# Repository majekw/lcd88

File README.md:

lcd88
=====

Open source, flexible PPM coder/mixer/brain for R/C transmitter.

Main website: http://majek.mamy.to/lcd88

About
-----

LCD88 is software for Atmega88/168/328 controller to generate PPM waveform.
It also support simple keyboard and graphic LCD.
Main goal of this project is to make cheap and powerful replacement for old
R/C transmitters. So, for few $ you could retrofit your old TX to make
fully programmable 8 channels (or more) transmitter.

Configuring
-----------

1. Open Makefile
2. Uncomment one of defines with processor type (M88, M168 or M328)
3. Uncomment clock selection (FCK16 for 16MHz or FCK11 for 11.0592MHz).
If you need another clock, you need to hack a little in lcd88.asm,
but don't set it higher than 16MHz!
4. Open lcd-s65.asm
5. Uncomment one define with lcd_l2f50, lcd_ls020 or lcd_st7735 depending
on you lcd hardware

Compiling/burning
---------

You need [AVRA](http://avra.sourceforge.net) to compile it.
Also some 'make' and Linux environment could help :-)
If you have Linux, just type 'make' and it should make everything.
Right now it's not very friendly for other systems, so in case of troubles,
look into Makefile and try make all steps manually.

After succesful compilation you should have 2 .hex files:
- lcd88.hex
- bootloader.hex

Bootloader image you must burn using USBASP or other 'traditional'
programmer. Then you could transfer lcd88.hex converted to raw binary
over serial.

Hardware
--------

Of course, you need some hardware to run this software :-)

Processors supported:
- Atmega88 (but support for it will be discontinued soon)
- Atmega168 and Atmega328 (both you can find on Arduino boards)

Processor clock supported: up to 16MHz (so, everything below or equal
will run fine).

Graphic LCD:
- 176x132 lcd used in old Siemens S65 phones, L2F50 and LS020 versions
- cheap 1.8" 160x128 tft based on ST7735, Arduino's GTFT should also work

Keyboard: it's only one part that you must do yourself as it's non standard.
Schematic is in pcb/ directory (Eagle files)
Required:
- 6 tact switches
- 6 diodes 1N4148
- 3 resistors about 1-10k

Depending on AVR voltage and variant of LCD, level converter also could
be required.

For more info about hardware look at http://majek.mamy.to/en/lcd88-hardware/
Models
------

Of course you need some models definitions:-)

For now, look into models.asm and try to figure out yourself how it works :-)
More info how blocks works is at http://majek.mamy.to/en/lcd88-how-it-works/

Author(s)
---------

Most of code made by Marek Wodzinski

Hardware specific code for S65 lcd based on C sources from Christian Kranz
(L2F50_display4.02 at http://www.superkranz.de/christian/S65_Display/DisplayIndex.html )

Fonts: 8x8 I got from Linux sources, other fonts are probably from open source
projetcs I don't remember :-(

m88def.inc, m168def.inc and m328def.inc are made by Atmel.

License
-------

All work is under GPL v3 license available in LICENSE file.

I'm not responsible in any way for uses or misuses of this code.
Use it at your own risk!

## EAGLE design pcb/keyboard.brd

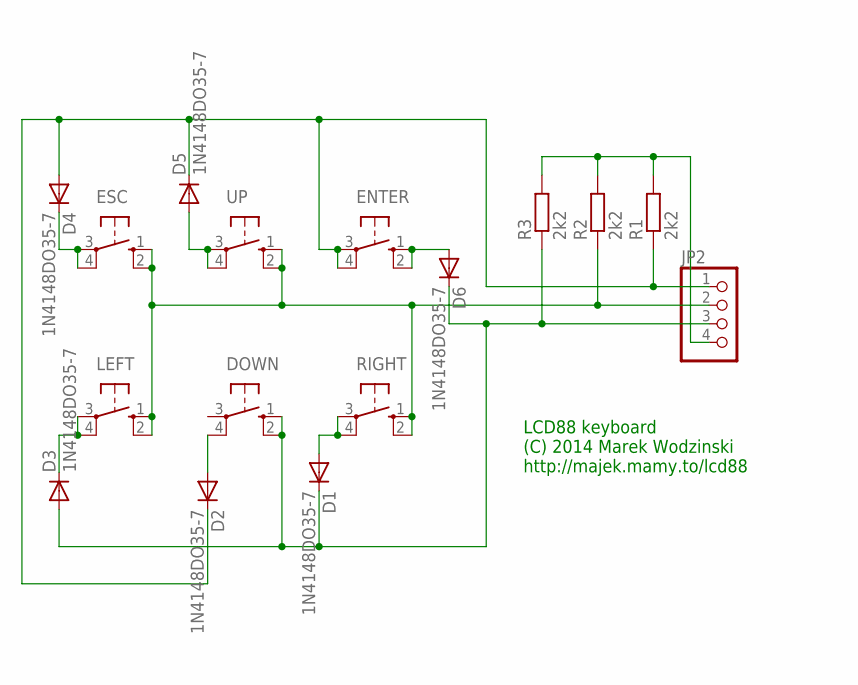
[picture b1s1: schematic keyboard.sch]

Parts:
D1, D2, D3, D4, D5, D6: 1N4148DO35-7; DO35-7
DOWN: 10-XX; B3F-10XX
ENTER: 10-XX; B3F-10XX
ESC: 10-XX; B3F-10XX
JP2: PINHD-1X4; 1X04
LEFT: 10-XX; B3F-10XX
R1, R2, R3: 2k2; R0805W
RIGHT: 10-XX; B3F-10XX
UP: 10-XX; B3F-10XX

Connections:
unnamed: ESC.1 (S), ESC.2 (S1), JP2.2, LEFT.1 (S), LEFT.2 (S1), R2.1, RIGHT.1 (S), RIGHT.2 (S1), UP.1 (S), UP.2 (S1)
unnamed: D2.A, DOWN.4 (P1)
unnamed: D4.C, ESC.3, ESC.4 (P1)
unnamed: D5.A, UP.3, UP.4 (P1)
unnamed: D2.C, D4.A, D5.C, ENTER.3, ENTER.4 (P1), JP2.1, R1.1
unnamed: D6.A, ENTER.1 (S), ENTER.2 (S1)
unnamed: D3.C, LEFT.3, LEFT.4 (P1)
unnamed: D1.A, RIGHT.3, RIGHT.4 (P1)
unnamed: D1.C, D3.A, D6.C, DOWN.1 (S), DOWN.2 (S1), JP2.3, R3.1
PLUS: JP2.4, R1.2, R2.2, R3.2

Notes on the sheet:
LCD88 keyboard (C) 2014 Marek Wodzinski http://majek.mamy.to/lcd88

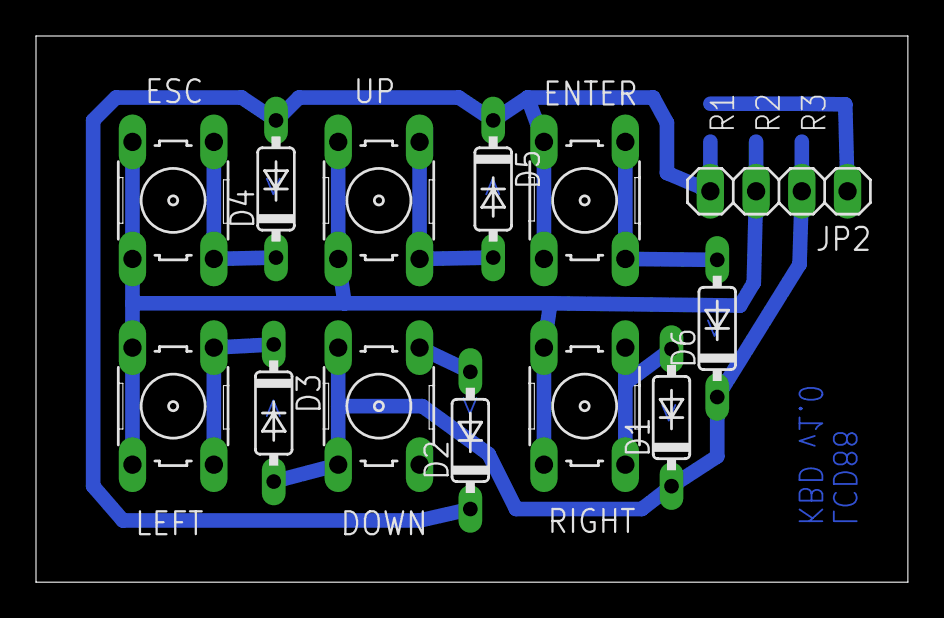
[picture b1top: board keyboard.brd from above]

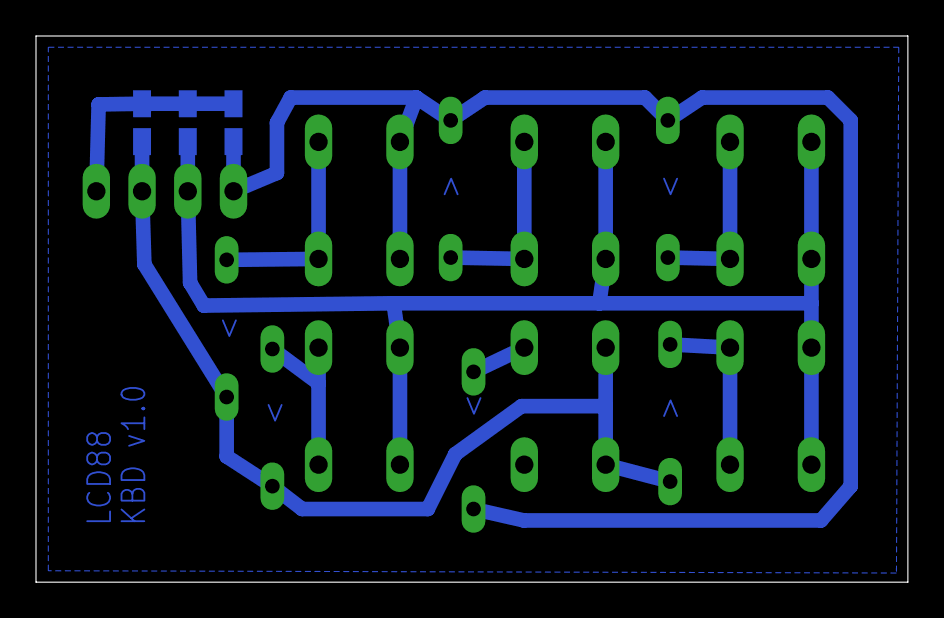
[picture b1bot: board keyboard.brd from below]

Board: 2 copper layers, 48.4 x 30.3 mm, 16 parts (3 on the bottom side), 10 nets.

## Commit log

2009-05-31 dodany inc, wywalone kodowanie calkiem
2009-06-01 dodane lcd (na razie nie dziala)
2009-06-08 troche przerobione lcd pod obrocone pismo, timer pod przetwornice dziala, troche poczyszczony kod
2009-06-10 dziala lcd, podswietlenie
2009-06-14 zmieniony lekko bootloader, dodana obsluga klawiatury
2009-06-15 naprawiony bug niezachowania itemp w kbd_scan
2009-06-15 czyszczenie ramu, pojedynczy bajt na klawiature, fixy
2009-06-18 poczatek matematyki
2009-06-19 pierdolka
2009-07-11 dzialajacy kod adc
2009-07-11 dodany filtr cyfrowy dla adc
2009-07-12 wstep do ppm;
2009-07-12 troche zmian w adc (wyzwalanie co 20ms z t2cm), wstep do generowania ppm
2009-07-13 dodany kod ppm, ale nie dziala
2009-07-14 ppm code works!
2009-07-14 dodane definicje modeli, limity w ppm, drobiazgi
2009-07-15 model delty skonczony
2009-07-17 ladowanie modelu do pamieci
2009-07-19 trims_find dziala, w load_model jest mega bug - do poprawki
2009-07-19 naprawiony model_load (chyba dziala)
2009-07-26 komentarz
2009-08-15 dodany multitasking, troche komentarzy, troche odsmiecenia
2009-08-15 komentarze, porzadki, naprawiony load_model, wyswietlanie nazwy aktualnego modelu, eeprom_init skonczony
2009-08-16 status inicjalizowany z eeproma, makra dla eeproma, uwzglednienie polazyzacji ppm, glowna petla task_calc, dodana biblioteka matematyczna
2009-08-20 zapisanie statusow operacji matematycznych przy przelaczaniu taskow, skonczony mul, dup i dodane blokowanie przerwan przy uaktualnieniu math_sp
2009-09-08 kosmetyka
2009-09-13 math_set/get_sp
2009-09-13 delta uzywa neg zamiast *-1
2009-09-13 naprawione 2 brzydkie bugi w math_calc_sign i mach_add
2009-09-13 obsluga kilku pierwszych blokow (dodaj, trim, rewers, mul)
2009-09-14 slupki kanalow wyjsciowych
2009-09-14 dodane do math: min, max, compare
2009-09-21 przymiarka pod extender: trzeba poprzestawiac kanaly...
2009-11-08 komentarze i ustawienie na stale na razie polaryzacji
2009-11-11 przerobione modele na nowy uklad kanalow
2009-11-11 zmiana nazwy miejsca na dane na storage, odczytywanie konca storage z eeproma w odpowiednich funkcjach (model_find i trims_find)
2009-11-11 skonczone show_out_bars
2009-11-12 definicja menu (formalna i dane)
2009-11-17 testowo zamieniony mnoznik w delcie z 0.5 na 1
2009-11-17 zrobiona linia statusu, wylaczony debug
2009-11-20 przerobione menu, czesc procedury pokazujacej menu
2009-11-23 przerobki pokazywania menu (nie skonczone)
2009-11-23 rysowanie menu skonczone
2009-11-23 wyszukiwanie kolejnych itemow w menu (nie testowane)
2009-11-25 nawigacja po menu dziala
2009-11-25 poprawka w menu, inicjalizacja statush, testy w main loop
2009-11-26 dodane storage_start/end/skip/find, trims_find przepisane z uzyciem storage_
2009-12-03 w polowie zmian - 2 linijki
2009-12-21 zmiana kolejnosci zmiennych math_
2010-06-11 dodany adres funkcji zapisujÄ cej do flashu
2010-06-11 uzycie pagesize zamiast liczby, troche komentarzy
2011-05-25 komentarz w math, porzadki
2011-11-11 dodane generowanie bootloader.inc
2011-11-11 usuniecie sladow po szyfrowaniu z bootloadera
2012-04-29 dodane labele dla bootloadera
2012-07-21 dodany model auta
2012-09-12 zmiany w makefile, bootloader dla m88 i m168
2012-09-12 usiniety hex dla bootloadera
2012-09-12 dodany naglowek dla m168, dodany konwerter hex2bin
2012-09-12 mala poprawka skryptu generujacego bootloader.inc
2012-09-12 fix na makefile, dalsza czesc m168
2012-09-14 maÅla zmiana komentarza
2012-09-14 fix do m88/168, fix w bootloaderze na pagesize
2012-09-16 komentarz do bootloader
2012-12-27 uruchamianie tylko na reset, zmiana kolejnosci programowania flasha
2012-12-27 fix dla tablicy wektorow dla m168/328
2012-12-27 wsparcie dla mega328
2012-12-27 fix buga temp3=0
2012-12-27 fix/workaround dla .ifndef
2012-12-27 avrdude w makefile, poprawiona zaleznosc or innych plikow asm
2012-12-27 update do m88
2012-12-27 +math_drop i math_push
2012-12-27 kolejna poprawka zaleznosci makefile
2012-12-27 wejscie cyfrowe
2012-12-28 dodane modele w zaleznosciach makefile
2012-12-28 dodany nowy model 8ch
2012-12-28 poprawka wykorzystania math_compare
2012-12-28 troche porzadkow, fix na math_compare, nowy klocek copy
2012-12-28 wywalony caly kod menu, jakies drobiazgi kosmetyczne
2012-12-29 +math_todec, math_pop
2012-12-29 drobna optymalizacja w tohex
2012-12-29 fixik na czyszczenie ramu:-)
2012-12-29 poprawka w math_todec
2012-12-29 strona z wartosciami i/o, troche optymalizacji i porzadkow
2012-12-29 poczatki obslugi menu
2012-12-30 klawisze w menu_loop skonczone
2012-12-30 dodane main_menu, dziala menu_debug:-)
2012-12-30 zakomentowane troche zbednych komentarzy
2012-12-30 +model_select, maÅle fixy
2012-12-31 zmiana kanalow trymerow i rewersow
2013-01-01 dodany math_todec_byte
2013-01-01 dodane menu_ram, przerobione menu i menu_keys
2013-01-02 wywalenie jednego modelu dla zwolnienia flasha
2013-01-02 komentarzyk
2013-01-05 mala optymizacja rozmiaru
2013-01-06 kalibracja drazkow dla mojej aparatury
2013-01-06 szukanie konca storage, ostatni model jest w koncu zapamietywany
2013-01-06 przerobka storage_find
2013-01-06 zmiana w storage_skip_current, wywalony storage_get_end
2013-01-07 kolejne 4 bajty:-)
2013-01-07 maly komentarz w makefile
2013-01-07 zmiana po testach na inny procek
2013-01-07 poprawka task_calc, poprawka menu_ram, zmienione menu modeli, poczatek trimow
2013-01-08 podmianka rejestru w math_todec
2013-01-08 trymery!
2013-01-09 dodane eeprom_read, przemeblowania
2013-01-09 trochÄe komentow w modelach
2013-01-09 trymery w eepromie! :-)
2013-01-10 poprawka dla delty
2013-01-10 dodany opis expo
2013-01-10 reverse
2013-01-10 dodane expo do delty
2013-01-10 dodane expo
2013-01-10 poszerzony stos math
2013-03-02 menu dla expo, info
2013-03-02 wsparcie dla Arduino Pro mini, komentarze, uzywanie wszedzie F_CPU zamiast ZEGAR czy hardcodowanych wartosci
2013-03-03 porzadki z zegarami i typami prockow
2013-03-03 tymczasowy commit z st7735
2014-01-05 skonczone st7735, troche porzadkow
2014-06-18 GPL license file added
2014-06-22 Added info about GPL license Updated README.md Added bootloader hex for Atmega328@16MHz (for Arduino Pro Mini)
2014-06-22 Added note about Atmel's include files
2014-06-22 removed leftovers of Atmega8 support from bootloader
2014-06-23 Optimization of hardware spi_tx
2014-06-23 Added keyboard Eagle files, README update
2014-06-24 Use constants instead of some cryptic values in models.asm Use offset to constants in channels definition. It could help if number of channels in transmitter change.
